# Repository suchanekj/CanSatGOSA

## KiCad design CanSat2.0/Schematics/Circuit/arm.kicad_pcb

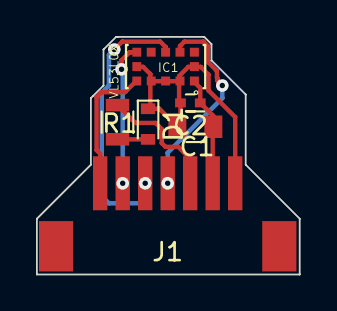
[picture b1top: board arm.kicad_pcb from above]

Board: 2 copper layers, 14.6 x 13.2 mm, 6 parts (0 on the bottom side), 8 nets.

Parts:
C1: 100nF; C_0805
C2: 4.7uF; C_0402
D1: LED; D_0603
IC1: VL53L0X; XDCR_VL53L0CXV0DH%2f1
J1: Conn_01x07; MOLEX_PicoBlade_7
R1: 150; R_0805

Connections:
+3V3: C1.1, C2.1, IC1.1, J1.6
/INT: IC1.7, J1.2
/LED: J1.5, R1.2
/SCL: IC1.10, J1.4
/SDA: IC1.9, J1.3
/XSHUT: IC1.5, J1.1
GND: C1.2, C2.2, D1.1, IC1.2, IC1.3, IC1.4, IC1.6, IC1.12, J1.7
unnamed: D1.2, R1.1

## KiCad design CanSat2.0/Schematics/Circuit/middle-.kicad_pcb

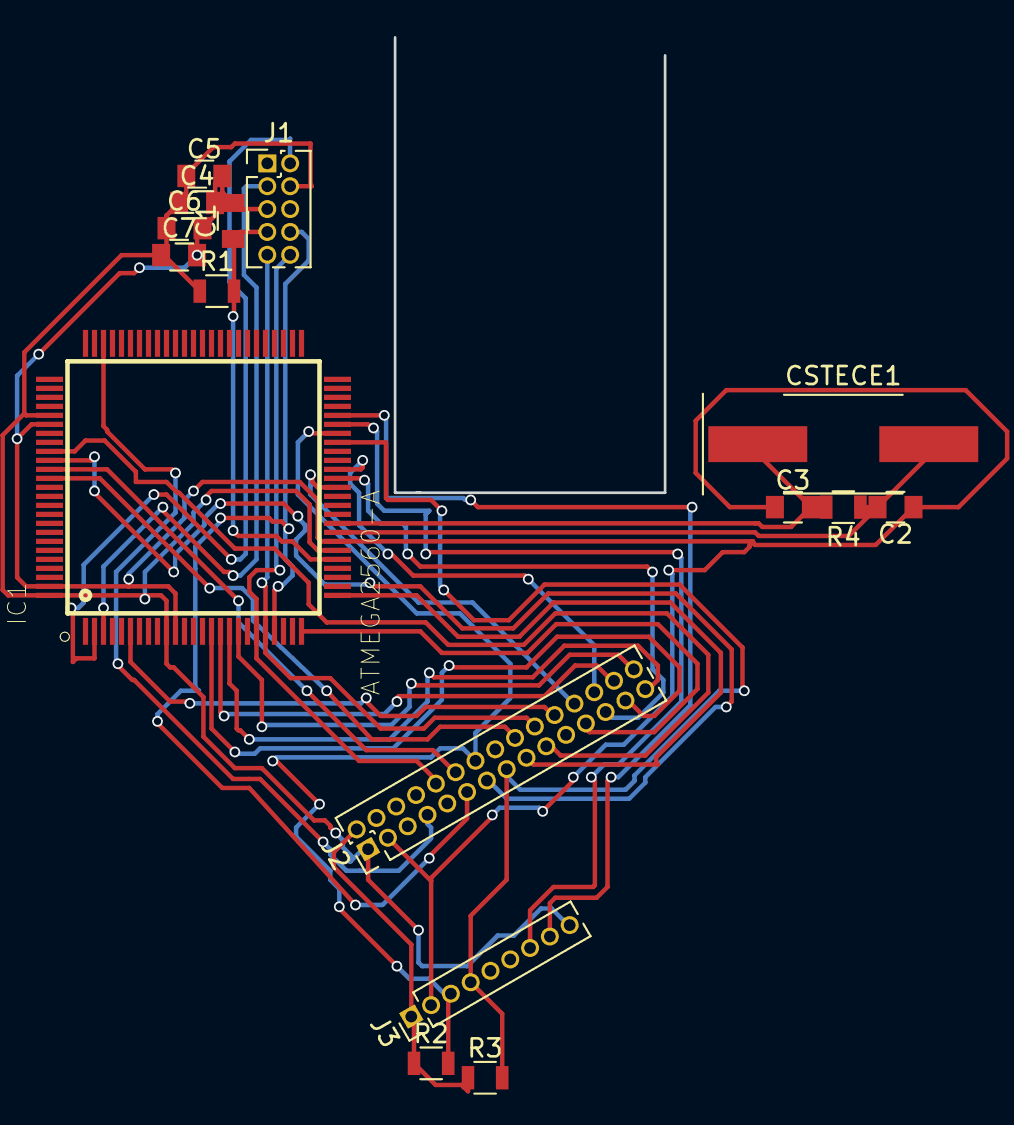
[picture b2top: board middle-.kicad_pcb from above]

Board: 2 copper layers, 16 parts (0 on the bottom side), 30 nets.

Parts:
C1: 22 pF; C_0805
C2, C3: 20 pF; C_0805
C4, C5, C6, C7: 100 nF; C_0805
CSTECE1: 16MHZ; Crystal_SMD
IC1: ATMEGA2560-A; AtMega2560-AU
J1: Conn_02x05_Counter_Clockwise; Pin_Header_Straight_2x05_Pitch1.27mm
J2: Main connector; Pin_Header_Straight_2x15_Pitch1.27mm
J3: Conn_01x09; Pin_Header_Straight_1x09_Pitch1.27mm
R1: 10k; R_0805
R2, R3: 2k; R_0805
R4: 1M; R_0805

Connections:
+3V3: J2.2, J3.1, R2.1, R3.1
+5V: C4.1, C5.1, C6.1, C7.1, IC1.10, IC1.31, IC1.80, IC1.100, J1.4, J2.1, J3.9, R1.1
/CO2: IC1.85, J2.13
/FC_PWM_1: IC1.18, J2.30
/FC_PWM_2: IC1.17, J2.29
/FC_PWM_3: IC1.16, J2.28
/FC_PWM_4: IC1.15, J2.27
/FC_PWM_5: IC1.40, J2.26
/FC_PWM_6: IC1.39, J2.25
/FC_PWM_7: IC1.38, J2.24
/FC_PWM_8: IC1.25, J2.23
/GSM_KEY: IC1.73, J2.7
/MISO: IC1.22, J1.8, J2.11
/MOSI: IC1.21, J1.9, J2.20
/O2: IC1.86, J2.12
/O3: IC1.84, J2.19
/RFM_INT: IC1.6, J2.22
/RST: C1.1, IC1.30, J1.7, R1.2
/RX: IC1.2, J1.2
/RX_GPS: IC1.45, J3.7
/SCK: IC1.20, J1.10, J2.10
/SCL: IC1.44, J2.14, J3.3, R2.2
/SDA: IC1.43, J2.15, J3.4, R3.2
/SERVO: IC1.26, J2.17
/TX: IC1.3, J1.3
/TX_GPS: IC1.46, J3.8
/V_READ: IC1.87, J2.18
/XTAL1: C2.2, CSTECE1.2, IC1.33, R4.1
/XTAL2: C3.2, CSTECE1.1, IC1.34, R4.2
GND: C1.2, C2.1, C3.1, C4.2, C5.2, C6.2, C7.2, IC1.11, IC1.32, IC1.81, IC1.99, J1.5, J2.3, J3.2

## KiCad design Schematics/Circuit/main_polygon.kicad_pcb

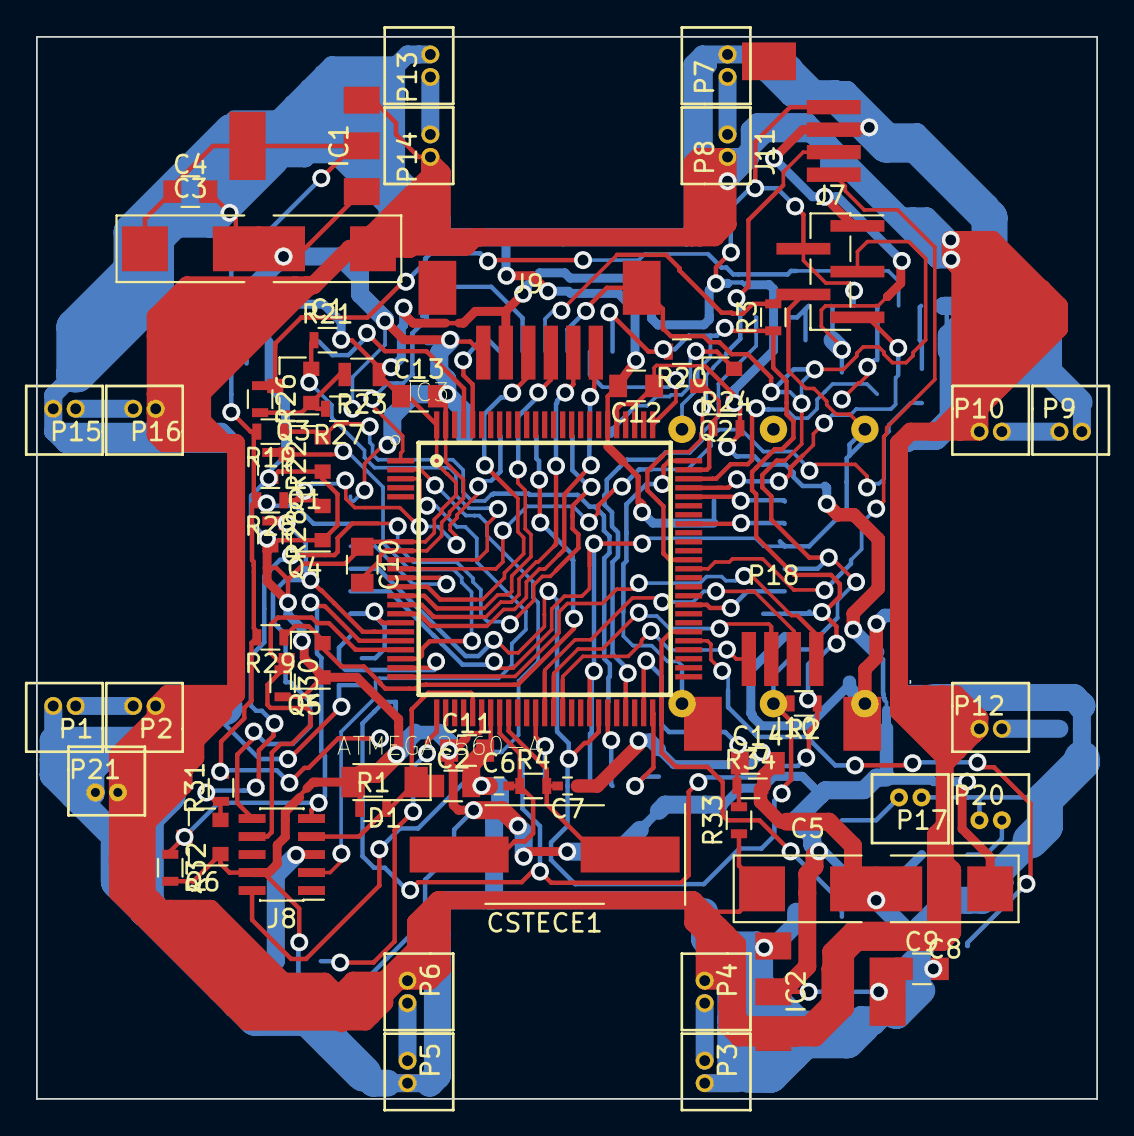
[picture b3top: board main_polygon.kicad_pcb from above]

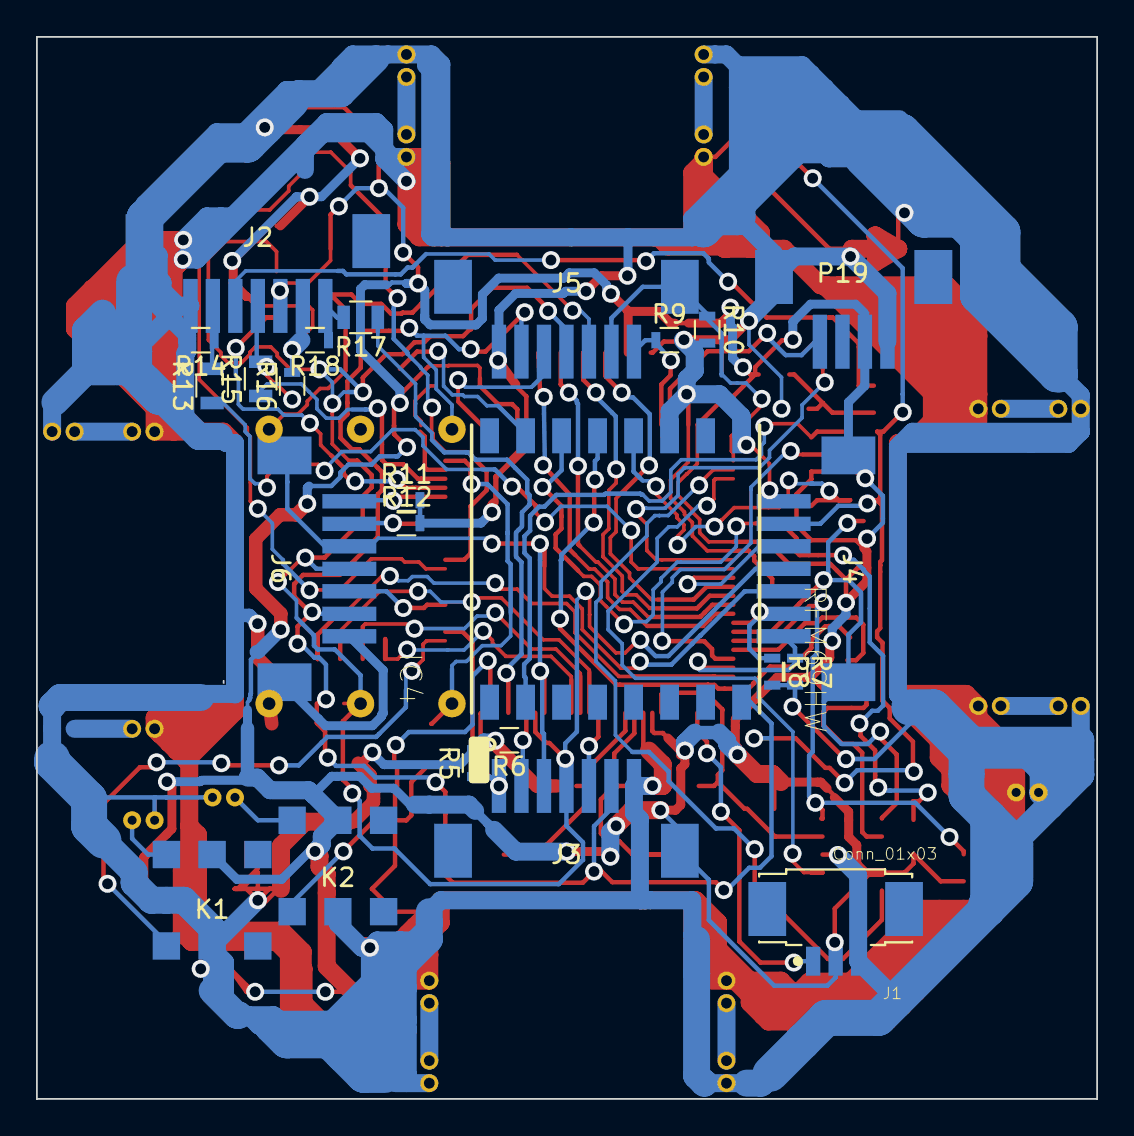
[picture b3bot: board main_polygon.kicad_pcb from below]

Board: 2 copper layers, 58.9 x 59.0 mm, 93 parts (24 on the bottom side), 68 nets.

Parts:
C1: 47 uF; CP_Tantalum_Case-U_EIA-6032-15_Reflow
C2: 22 pF; C_0805
C3, C5, C8: 47 uF; CP_Tantalum_Case-C_EIA-6032-28_Reflow
C4, C9, C10, C11, C12, C13, C14: 100 nF; C_0805
C6, C7: 20 pF; C_0402
CSTECE1: 16MHZ; Crystal_SMD
D1: CD1206-S01575; D_MiniMELF
IC1: NCP1117ST33T3G; ncp1117
IC2: NCP1117ST50T3G; ncp1117
IC3: ATMEGA2560-A; AtMega2560-AU
IC4: RFM69HW; XCVR_RFM95W-868S2
J1: Conn_01x03; MOLEX_0532610371
J2, J3, J4, J5, J6: Conn_01x07; MOLEX_PicoBlade_7
J7: Conn_01x05; Pin_Header_Straight_1x05_Pitch1.27mm_SMD_Pin1Right
J8: Conn_02x05_Counter_Clockwise; Pin_Header_Straight_2x05_Pitch1.00mm_SMD
J9: Conn_01x06; MOLEX_PicoBlade_6
J10, J11: Conn_01x04; MOLEX_PicoBlade_4
K1, K2: HESOP1; SMD_6pin_IC
P1, P2, P3, P4, P5, P6, P7, P8, P9, P10, P12, P13, P14, P15, P16, P17, P20, P21: CONN_2; MOLEX_PicoBlade_2
P18: CONN_3X2; co2
P19: CONN_O2; MOLEX_PicoBlade_4
Q1, Q2, Q3, Q4, Q5, Q6: BSS138; SOT-23
R1, R5, R6, R7, R8, R9, R10, R11, R12, R19, R20, R21, R22, R24, R25, R26, R28, R29, R30, R31, R32, R34: 10k; R_0603
R2, R3: 2k; R_0603
R4: 1M; R_0603
R13, R15, R17, R23: 2k2; R_0805
R14, R16, R18, R27: 2k8; R_0603
R33: 20k; R_0603

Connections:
+3V3: C3.1, C4.1, IC1.2, IC4.8, J3.6, J4.6, J5.6, J6.6, P18.2, R2.1, R3.1, R19.2, R20.2, R25.2, R29.2, R31.2
+5V: C8.1, C9.1, C10.1, C11.1, C12.1, C13.1, D1.2, IC2.2, IC3.10, IC3.31, IC3.80, IC3.100, J1.2, J2.3, J7.2, J8.4, J9.5, J11.1, K1.5, K2.5, P19.2, Q1.1, Q2.1, Q4.1, Q5.1, Q6.1, R1.1, R21.2, R22.2, R23.1, R24.2, R28.2, R30.2, R32.2
+12V: C1.1, C5.1, IC1.3, IC2.3, P2.2, P4.2, P6.2, P8.2, P10.2, P12.2, P14.2, P16.2, P21.1, R33.1
/CAM_PWR: K1.6, P20.1
/CAM_TRIG: IC3.55, K1.1
/CO2: IC3.75, P18.1
/FLY_PWR: K2.6, P17.1
/FLY_TRIG: IC3.56, K2.1
/INT1: IC3.45, J3.2, R6.1
/INT2: IC3.1, J5.2, R10.1
/INT3: IC3.19, J4.2, R8.1
/INT4: IC3.68, J6.2, R12.1
/LED1: IC3.37, J3.5
/LED2: IC3.76, J5.5
/LED3: IC3.14, J4.5
/LED4: IC3.59, J6.5
/LED_TOP: IC3.72, J7.5
/MISO: IC3.22, J8.8, Q5.3, R30.1
/MOSI: IC3.21, J8.9, Q6.3, R32.1
/O2: IC3.97, P19.4
/PWM1: IC3.18, J9.1
/PWM2: IC3.17, J9.2
/PWM3: IC3.16, J9.3
/PWM4: IC3.15, J9.4
/PWM5: IC3.40, J10.1
/PWM6: IC3.39, J10.2
/PWM7: IC3.38, J10.3
/PWM8: IC3.25, J10.4
/PWRKEY: IC3.73, R15.1
/RFMINT: IC4.2, Q1.2, R19.1
/RFM_INT: IC3.23, Q1.3, R22.1
/RST: C2.1, D1.1, IC3.30, J8.7, R1.2
/RX: IC3.2, J8.2
/RXD-GSM: IC3.13, R13.1
/RX_GPS: IC3.63, J11.4
/SCK: IC3.20, J8.10, Q4.3, R28.1
/SCL: IC3.44, J3.4, J4.4, J5.4, J6.4, J7.3, P18.3, R2.2
/SDA: IC3.43, J3.3, J4.3, J5.3, J6.3, J7.4, P18.6, R3.2
/SERVO: IC3.26, J1.1
/SLEEP-GSM: IC3.47, R17.1
/SS: IC3.74, Q2.3, R24.1
/TX: IC3.3, J8.3
/TXD-GSM: IC3.12, Q3.2, R21.1
/TX_GPS: IC3.64, J11.3
/V_READ: C14.1, IC3.49, R33.2, R34.1
/XSHUT1: IC3.50, J3.1, R5.1
/XSHUT2: IC3.96, J5.1, R9.1
/XSHUT3: IC3.24, J4.1, R7.1
/XSHUT4: IC3.71, J6.1, R11.1
/XTAL1: C6.2, CSTECE1.2, IC3.33, R4.1
/XTAL2: C7.2, CSTECE1.1, IC3.34, R4.2
GND: C1.2, C2.2, C3.2, C4.2, C5.2, C6.1, C7.1, C8.2, C9.2, C10.2, C11.2, C12.2, C13.2, C14.2, IC1.1, IC2.1, IC3.11, IC3.32, IC3.81, IC3.99, IC4.9, IC4.11, J1.3, J2.2, J2.7, J3.7, J4.7, J5.7, J6.7, J7.1, J8.5, J9.6, J11.2, K1.2, K2.2, P1.1, P3.1, P5.1, P7.1, P9.1, P13.1, P15.1, P17.2, P18.5, P19.1, P20.2, P21.2, R5.2, R6.2, R7.2, R8.2, R9.2, R10.2, R11.2, R12.2, R14.2, R16.2, R18.2, R27.1, R34.2
unnamed: IC4.12, Q4.2, R25.1
unnamed: IC4.13, Q5.2, R29.1
unnamed: IC4.14, Q6.2, R31.1
unnamed: IC4.15, Q2.2, R20.1
unnamed: J2.1, R17.2, R18.1
unnamed: J2.4, R15.2, R16.1
unnamed: J2.5, Q3.3, R26.1
unnamed: J2.6, R13.2, R14.1
unnamed: P1.2, P2.1
unnamed: P3.2, P4.1
unnamed: P5.2, P6.1
unnamed: P7.2, P8.1
unnamed: P9.2, P10.1
unnamed: P13.2, P14.1
unnamed: P15.2, P16.1
unnamed: Q3.1, R23.2, R26.2, R27.2
